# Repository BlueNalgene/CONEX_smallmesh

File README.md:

# CONEX_smallmesh
Resources for 2021 CONEX Sensor deployment for CO_2, CH_4, T, Rh, P sensing.

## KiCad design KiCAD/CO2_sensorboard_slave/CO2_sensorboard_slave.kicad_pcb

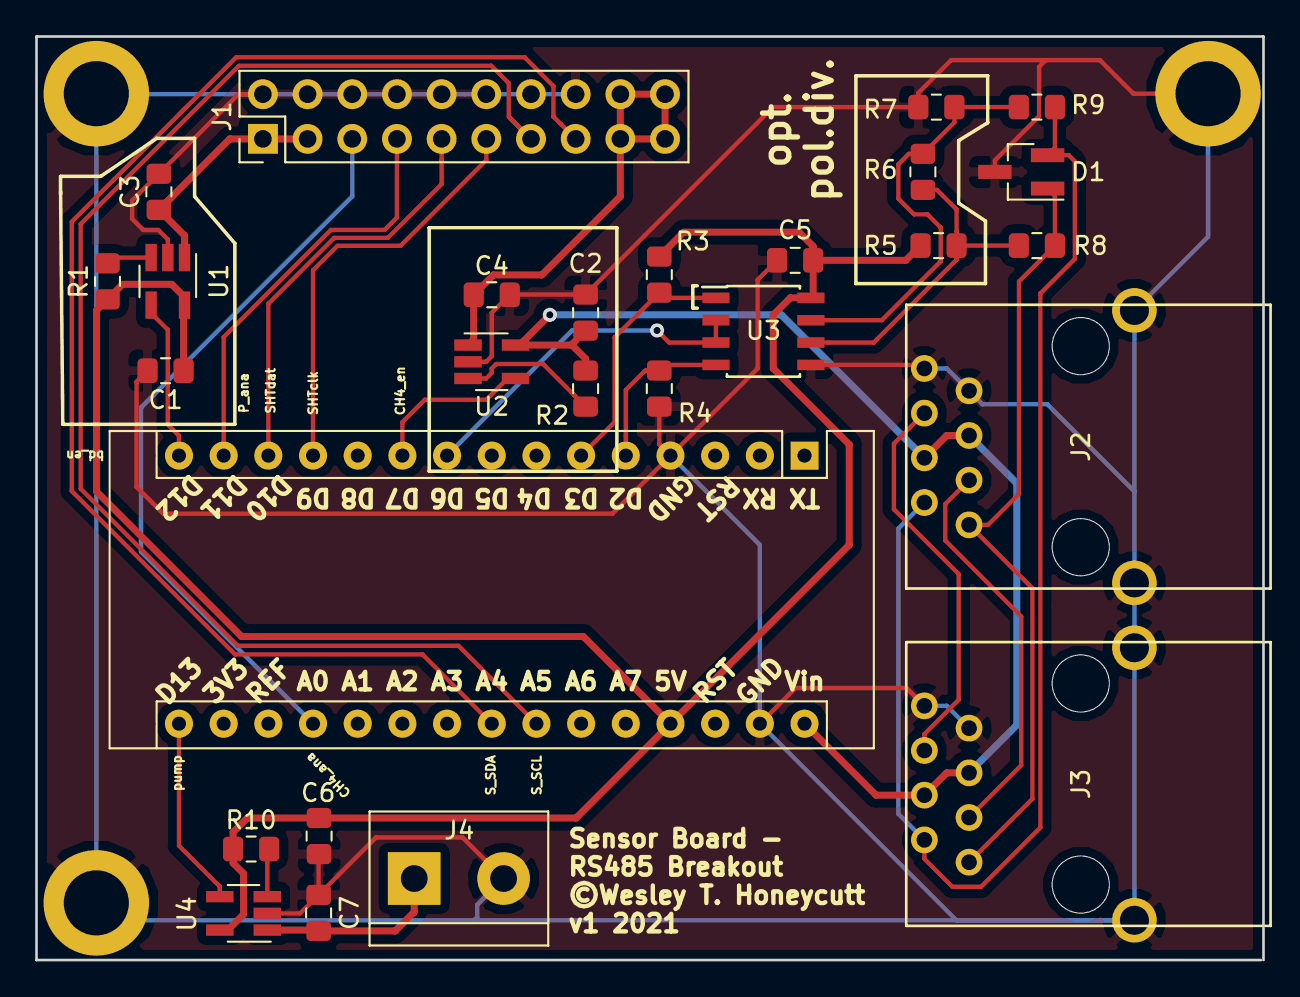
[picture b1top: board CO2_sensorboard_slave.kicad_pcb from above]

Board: 2 copper layers, 69.8 x 52.5 mm, 30 parts (0 on the bottom side), 27 nets.

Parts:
A1: Arduino_Nano_v3.x; Arduino_Nano
C1, C2, C3, C4, C6, C7: 10uF; C_0805_2012Metric_Pad1.15x1.40mm_HandSolder
C5: 0.1uF; C_0805_2012Metric_Pad1.15x1.40mm_HandSolder
D1: CDSOT23-SM712 (SP0502BAHT); SOT-23_Handsoldering
H1, H2, H4: MountingHole_Pad; MountingHole_3.7mm_Pad
J1: Conn_02x10_Odd_Even; PinHeader_2x10_P2.54mm_Vertical
J2, J3: RJ45_Shielded; SS7188SAPG41BA
J4: Screw_Terminal_01x02; TerminalBlock_bornier-2_P5.08mm
R1, R2, R3, R4, R10: 10k; R_0805_2012Metric_Pad1.15x1.40mm_HandSolder
R5, R7: 1k; R_0805_2012Metric_Pad1.15x1.40mm_HandSolder
R6: 120u; R_0805_2012Metric_Pad1.15x1.40mm_HandSolder
R8, R9: 10u; R_0805_2012Metric_Pad1.15x1.40mm_HandSolder
U1, U2, U4: DIO7063_SOT23-5; SOT-23-5_HandSoldering
U3: SN888C (SP3485EN); SOIC-8_3.9x4.9mm_P1.27mm

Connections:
+5V: A1.27, C1.1, C5.1, C6.1, R1.1, R3.1, R5.1, R10.1, U1.5, U3.8, U4.5
CH4_ana: A1.19, J1.5
CH4_en: A1.10, U2.4
GND: A1.4, A1.29, C1.2, C2.2, C3.2, C4.2, C5.2, C6.2, C7.2, D1.3, H1.1, H2.1, H4.1, J1.2, J1.4, J1.6, J1.8, J1.10, J1.12, J1.14, J1.16, J2.7, J2.8, J2.SH, J3.7, J3.8, J3.SH, J4.2, R4.2, R7.2, U1.2, U2.2, U3.5, U4.2
unnamed: A1.5, R4.1, U3.4
unnamed: A1.6, R3.2, U3.1
unnamed: A1.9, U3.2, U3.3
unnamed: C3.1, J1.1, J1.3, U1.1
unnamed: C4.1, J1.17, J1.18, J1.19, J1.20, U2.1
unnamed: C7.1, J4.1, U4.1
unnamed: D1.1, J2.1, J3.1, R8.1
unnamed: D1.2, J2.2, J3.2, R9.1
unnamed: J2.3, J3.3
unnamed: J2.6, J3.6
unnamed: R1.2, U1.3
unnamed: R2.2, U2.3
unnamed: R5.2, R6.1, R8.2, U3.6
unnamed: R6.2, R7.1, R9.2, U3.7
unnamed: R10.2, U4.3
P_ana: A1.14, J1.7
SHTclk: A1.12, J1.11
SHTdata: A1.13, J1.9
S_SCL: A1.24, J1.13
S_SDA: A1.23, J1.15
VCC: A1.30, C2.1, J2.4, J2.5, J3.4, J3.5, R2.1, U2.5
bd_en: A1.15, U1.4
pump_en: A1.16, U4.4

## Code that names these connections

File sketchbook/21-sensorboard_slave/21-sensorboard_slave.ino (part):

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const uint8_t ch4Pin   = A0;

// Declare power switch pins
const uint8_t ch4_en   =  7; // MQ-4
const uint8_t bd_en    = 12; // Everything else on sensorboard
const uint8_t pump_en  = 13; // Air pump

// Declare pin value of our "Transmit Enable" for the RS485 connection
const uint8_t RS485_TE =  6;
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	
// 	mySerial.flush();
	
	pinMode(ch4_en, OUTPUT);
	digitalWrite(ch4_en, LOW);
	pinMode(bd_en, OUTPUT);
	digitalWrite(bd_en, HIGH);
	pinMode(pump_en, OUTPUT);
	digitalWrite(pump_en, LOW);
	
	Serial.println("setup complete");
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

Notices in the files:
sketchbook/21-sensorboard_slave/21-sensorboard_slave.ino:
License: GPL-3.0
KiCAD/CO2_sensorboard_slave/CO2_sensorboard_slave.kicad_pcb:
©Wesley T. Honeycutt
